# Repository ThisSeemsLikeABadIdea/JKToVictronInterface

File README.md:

# JKToVictronInterface - Replaced 

I'm not sure what happened but this no longer works with Esspressif IDF, I have replaced this with a new version (to be uploaded shortly), im leaving it here for reference until i can replace it entirely

A very rough start on an JK BMS interface for Victron Energy Systems

This is not an arduino project, its an espressif IDF project. (IDF 4.4)

You will need to familizarize yourself with it in order to make this work. Its not particularly difficult if you use VS Code. Simply install VS Code and use the espressif idf installer to install the correct version. (it will default to the latest version) 

The intention is to have a standalone device that can communicate the JKBMS details to Victron, But when using multiple devices instead of having a master node as a single point of failure i would like all the devices *when running more than one to become the master and take over. We live off grid and cant afford for a single device to cause our power to go out. 

A fair bit of of this repo has been snatched from DIY BMS, ESPHOME and others. 

Can tranceiver is connected to 
 Can_TX_GPIO_NUM             21
 Can_RX_GPIO_NUM             22
 the model number is WCMCU-230  (https://www.ebay.com.au/itm/393502933357) these things are hit and miss, sometimes they work othertimes they are duds

 The serial to JK-BMS is connected to
  #define JK_TX_PIN 16
  #define JK_RX_PIN 17

The main.c file is the espressif IDF app and entry point. 
  the main.c creates a task to run an instance of JKBMS and that has its own loop to pull data from the JKBMS
  main.c create a task for the TWAI interface

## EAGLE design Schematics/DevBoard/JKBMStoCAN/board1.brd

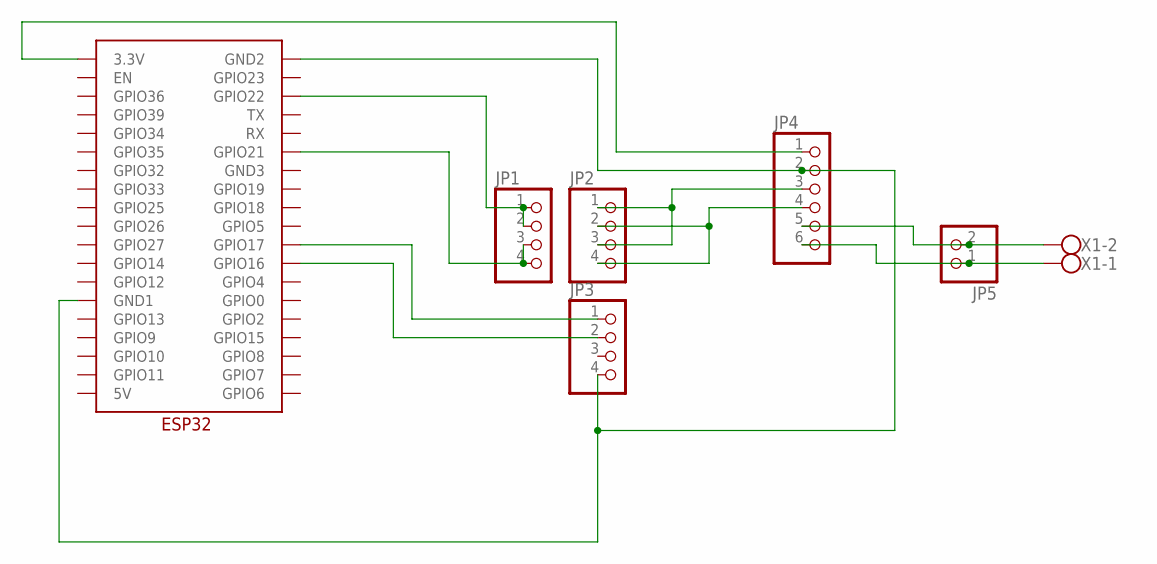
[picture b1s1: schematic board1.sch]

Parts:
JP1, JP2, JP3: PINHD-1X4; 1X04
JP4: PINHD-1X6; 1X06
JP5: PINHD-1X2; 1X02
U$1: ESP32_GRBL
X1: W237-102

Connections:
unnamed: JP3.4, JP4.2, U$1.GND1, U$1.GND2
unnamed: JP4.1, U$1.3.3V
unnamed: JP1.1, JP1.2, U$1.GPIO22
unnamed: JP1.3, JP1.4, U$1.GPIO21
unnamed: JP2.1, JP2.3, JP4.3
unnamed: JP4.5, JP5.2, X1.2
unnamed: JP2.2, JP2.4, JP4.4
unnamed: JP3.1, U$1.GPIO17
unnamed: JP3.2, U$1.GPIO16
unnamed: JP4.6, JP5.1, X1.1

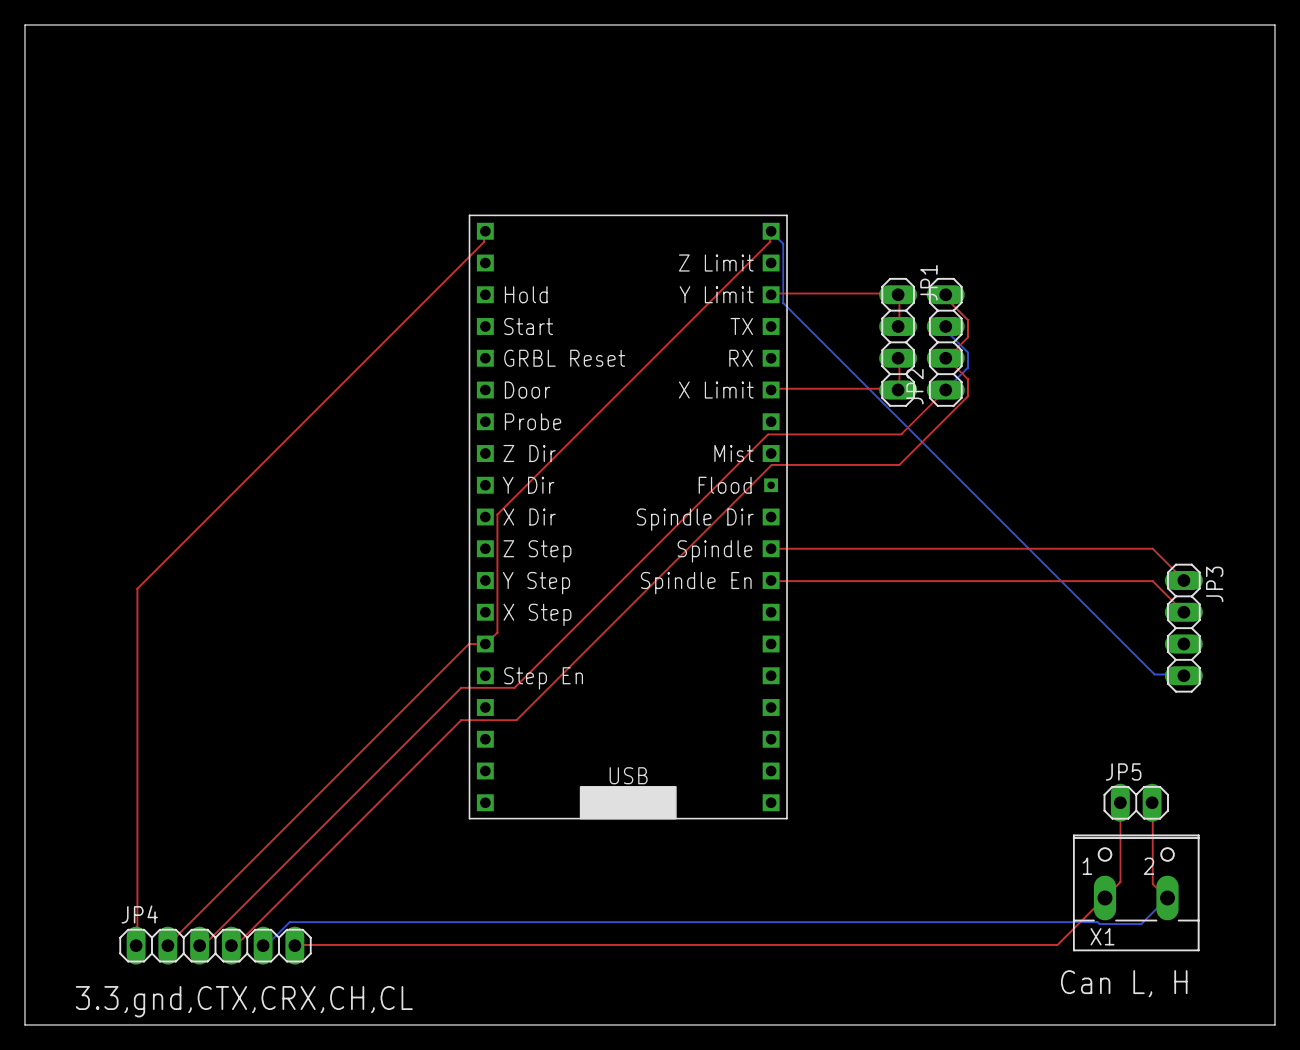
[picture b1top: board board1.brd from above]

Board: 2 copper layers, 100.0 x 80.0 mm, 7 parts (0 on the bottom side), 10 nets.

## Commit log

2024-01-13 Added the first schematic, it uses a CNC version of ESP32 footprint, it needs to be replaced. but it worked for me to get it out in a rush. the foot print is also slightly too narrow.
2024-01-13 Update README.md
    Just updaing the readme with some context.
2024-01-22 add prelim for wifi_prov mgr, mqtt client and web page handler
2024-04-01 rough pass on wifi manager and mqtt
2024-04-01 mqtt and wifimanager update pass2
2024-04-01 added sub component
